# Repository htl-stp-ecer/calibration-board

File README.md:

<div align="center">

# calibration-board

**A companion board for the KIPR Wombat: absolute position from optical flow, and a reference IMU good enough to calibrate the Wombat's own.**

KiCad PCB · STM32F722 firmware · On-board Madgwick fusion · Persistent flash calibration · USB-CDC to LCM bridge

> 📖 Platform documentation at [raccoon-docs.pages.dev](https://raccoon-docs.pages.dev/)

</div>

---

## What this is

There are two things a Wombat can't tell you well on its own.

The first is where it actually is. Wheel odometry integrates encoder ticks and trusts them, but wheels slip on seams, on poms and on ramps, and every slipped tick stays in the estimate for the rest of the run. Encoders measure the wheels, not the ground.

The second is whether its IMU is accurate. The Wombat's onboard IMU is fine for checking that a turn was roughly 90°. It isn't good enough to calibrate anything against.

This board addresses both, and it rides on the robot rather than sitting on a bench:

- A PAA5100 optical flow sensor tracks the table surface. Counts are scaled through a stored calibration into centimetres, which gives the robot an absolute position that doesn't depend on whether a wheel spun.
- An ICM-42688-P with Madgwick fusion on an M7 with an FPU provides a gyro reference accurate enough to calibrate the Wombat's onboard IMU against.

Hence the name. It isn't a board you calibrate, it's the board that does the calibrating.

### What it's for

- Calibrating the onboard IMU, with this board as the reference
- Motion teach-in, recording the trajectory that actually happened rather than the one the encoders inferred
- Automated setup routines. Botball allows automated routines during setup time, which is when a robot can locate and calibrate itself before the run starts

This repo isn't a template. It's a working board with an honest bring-up history attached. Read [Known limitations](#known-limitations) before fabbing one.

---

## Calibration that survives a power cycle

Most of the interesting work is in `app/src/paa_cal_module.c` and `app/inc/calib_store.h`.

Calibration lives in flash rather than in a startup routine. Sector 7 (0x08060000, 128 KB) holds a single 64-byte block: PAA scaling (`cx_per_cm`, `cy_per_cm`, `height_mm`), the gyro bias, a magic number, a schema version and a CRC32. The firmware fits in sectors 0 to 3, so 4 to 7 are free. A bad CRC or empty flash falls back to defaults and reports `valid = false`, so the caller knows it has never been calibrated instead of trusting garbage.

The board boots already calibrated. At startup the stored gyro bias is loaded straight into `imu_fusion_init()`, so there's no warm-up and no need to hold the robot still before a match.

Bias is learned continuously and persisted carefully. While the board is at rest, an exponential moving average runs on the raw gyro, and that average is the bias. It's subtracted before Madgwick and before anything is sent over USB. Auto-save only fires when the learned bias drifts more than 0.5 dps from the stored value, only while at rest so the value is trustworthy, and at most every 2 minutes. Each save costs a full sector erase, roughly 1 s and one P/E cycle, so the threshold and interval keep writes down to a few per large temperature swing. Gyro bias drifts around 0.05 dps/°C, which is what the thresholds are sized for.

Flash writes are deferred out of interrupt context into the main loop via a pending flag, because `HAL_FLASHEx_Erase` blocks.

At-rest detection uses a max-min spread across the gyro axes and accel magnitude, with time dwell and hysteresis. It takes about 0.5 s to declare the board still, and exits immediately on motion. Madgwick runs without a magnetometer at the ICM's 1 kHz ODR, so yaw drifts slowly while roll and pitch stay corrected against gravity. A filter step costs about 1 µs on the M7 at 216 MHz.

Commands over USB: `CMD_SET_PAA_CAL` stores new PAA scaling, `CMD_SAVE_GYRO_BIAS` persists the current at-rest average, `CMD_RESET_GYRO_BIAS` clears it. Telemetry goes the other way, with ORIENTATION frames (quaternion, bias, at-rest flag) at 100 Hz and PAA calibration telemetry at 1 Hz.

---

## How it fits together

```
PAA5100 ─┐                                              ┌─ raccoon/calib_board/paa/delta_x
         ├─ SPI ─► STM32F722 ──► USB-CDC ──► host ──────┤─ raccoon/calib_board/icm/accel
ICM-42688-P ─┘     fusion 1 kHz   binary     bridge     ├─ raccoon/calib_board/icm/gyro
                   cal in flash   frames                └─ raccoon/calib_board/status/*
```

`host/` is a C++ bridge (`raccoon-calib-bridge`) that reads binary frames from `/dev/ttyACM*` and republishes them as typed [raccoon-transport](https://github.com/htl-stp-ecer/raccoon-transport) messages. Calibration data flows on the same LCM channels as everything else in RaccoonOS, so BotUI or any other subscriber can plot it live. Status channels republish every second, which means a subscriber that starts late still picks up the current state instead of waiting for an event. A systemd unit is included.

### Firmware architecture

The module registry is Arduino-style. Each sensor is a `module_t` with `setup()` and `loop()`, registered in one array in `app/src/app.c`. An `enabled` flag parks a module without deleting it, which is how the dead BNO is handled.

Modules are started 25 ms apart rather than all at once. Every peripheral draws current at bring-up, and simultaneous init is a step load that can pull a marginal supply into brownout. Staggering flattens the ramp. The capacitor inrush at plug-in happens before this phase and isn't affected.

---

## Bring-up history

The board was designed around a Bosch BNO086, which does sensor fusion on-chip and outputs a quaternion directly. It never came up. After reset the INT line asserts, but the BNO never actively drives MISO, so every packet we read was a threshold artefact from a floating line. SPI mode, clock speed, pull-ups, boot delay and pin states were all ruled out in software, which left a suspected broken CS path. It's parked in the firmware with `.enabled = false /* BNO08x defekt */`.

The ICM-42688-P took over instead: raw 6-axis, with fusion left to us. That's why `imu_fusion.c` exists. Losing the chip that would have done fusion internally is what moved Madgwick onto the STM32, where the bias estimator could be added and the whole pipeline is visible rather than hidden behind a sensor hub.

The HSE crystal also refused to oscillate at first, leaving `HSEON=1, HSERDY=0` and dropping into `Error_Handler` on every boot. That turned out to be an oscillator ground problem and was fixed in the schematic. The firmware runs on HSE now.

---

## Repo layout

| Path | Contents |
|:-----|:---------|
| `Firmware/` | STM32CubeMX CMake project, target STM32F722RET6. Capitalised folders are ST-generated, lowercase are ours |
| `Firmware/app/` | Module registry, fusion, calibration store, USB framing |
| `Firmware/drivers/` | Our chip drivers: `bno08x/`, `icm42688p/`, `paa5100/` |
| `Firmware/lib/sh2/` | CEVA BNO08x driver (git submodule) |
| `Firmware/scripts/` | build / flash / debug / uart / swo. Call these rather than ST tools directly |
| `host/` | C++ USB-CDC to raccoon-transport bridge, plus systemd unit |
| `IMU_Extendor_Board/` | KiCad 7+ project: schematic, PCB, BOM, gerbers in `production/` |
| `enclosure/` | OpenSCAD tray and lid, STL/STEP exports (M2 self-tapping, ~55x55 mm PCB) |
| `Component_Datasheets/` | Datasheets plus hand-written analysis (`external_clock_analysis.md`) |
| `docs/` | Toolchain setup, firmware workflow, hardware overview, coding conventions |

---

## Quick start

```bash
git submodule update --init --recursive   # sh2 + raccoon-transport

Firmware/scripts/build.sh          # cmake + ninja
Firmware/scripts/build-docker.sh   # same, in a container, no host arm-gcc needed
Firmware/scripts/flash.sh          # build + flash + verify + start over ST-LINK SWD
Firmware/scripts/uart.sh           # stream the debug console (J703, 115200 8N1)
```

Full setup for a fresh machine: [`docs/toolchain-setup.md`](docs/toolchain-setup.md).

### Catching boot output

Start `uart.sh` before `flash.sh`. The boot `printf` fires within milliseconds of reset, well before you can switch terminals. Two panes:

```bash
# Pane 1, left running:
Firmware/scripts/uart.sh
# Pane 2:
Firmware/scripts/flash.sh
```

If an expected printf never appears, the firmware is more likely hung before that line than the UART is broken. Init exposes debug globals (`g_bno_init_status`, `g_paa_init_status`, `g_bno_stage`, `g_paa_cal_loaded`) that you can read over SWD without re-flashing:

```bash
STM32_Programmer_CLI -c port=SWD mode=HOTPLUG -r32 <addr> 4
```

### The USER LED is a status channel

With no UART adapter attached, the LED is the only thing reporting anything:

| Pattern | Meaning |
|:--------|:--------|
| 100 ms on / 100 ms off (fast) | init OK, sensor answered, product IDs read |
| 500 ms on / 500 ms off (slow) | setup failed, INT line or clock path suspect |
| 50 ms on / 950 ms off (pulse) | unexpected init return code |

---

## Known limitations

Worth reading before you fab a board or trust a number.

- The BNO086 is dead and disabled. A broken CS path is the suspicion. Software causes were ruled out, so it needs a DMM on `PA4` to `BNO086 CSN` before anyone touches the firmware again.
- USB-C (J101) is not populated. The board runs off the ST-LINK debug cable, which caps its current budget and means it isn't standalone. J101 and the USBLC6 ESD diode need populating per the schematic before it can ride on a robot properly.
- SWO doesn't work with ST-LINK V2 clones. `swo_init` configures TPIU/ITM correctly, but the green clones expose a `T_JTDO` pin that isn't internally wired to their TRACESWO input, and reflashing official ST firmware doesn't fix it. Use UART4 instead, or a genuine STLINK-V3. `__io_putchar` writes to both sinks, so take whichever you can capture.
- PAA scaling depends on mount height. The defaults assume 19 mm. Changing the height changes counts-per-cm, so recalibrate via `CMD_SET_PAA_CAL` after any remount or the absolute position will be confidently wrong.
- The flash layout assumes small firmware. The calibration block sits in sector 7 because the code fits in sectors 0 to 3. Firmware growing past about 448 KB breaks that.
- Chip-select assignments aren't fully captured in the firmware. Cross-reference the KiCad schematic before wiring up a new sensor.
- `Firmware.ioc` is owned by CubeMX. Regenerating overwrites most of `Core/` and `Drivers/`, so keep code inside the `USER CODE BEGIN/END` markers, or put it in `app/` and call it from `app_main()`.
- Parts of the docs and code comments are in German. This was an internal engineering repo and we haven't translated it.

---

## Part of RaccoonOS

| Repository | What it is |
|:-----------|:-----------|
| [raccoon-transport](https://github.com/htl-stp-ecer/raccoon-transport) | The LCM messaging layer this board publishes into |
| [stm32-data-reader](https://github.com/htl-stp-ecer/stm32-data-reader) | Pi to STM32 SPI bridge on the robot itself |
| [raccoon-lib](https://github.com/htl-stp-ecer/raccoon-lib) | Core robotics library, odometry and heading control downstream of this |
| [raccoon-robots](https://github.com/htl-stp-ecer/raccoon-robots) | Real competition robots built on the platform |
| [botui](https://github.com/htl-stp-ecer/botui) | Wombat dashboard, can subscribe to these channels live |
| [documentation](https://raccoon-docs.pages.dev/) | Full platform docs |

---

Built by team `axht-3085`, the Botball team at HTL St. Pölten.

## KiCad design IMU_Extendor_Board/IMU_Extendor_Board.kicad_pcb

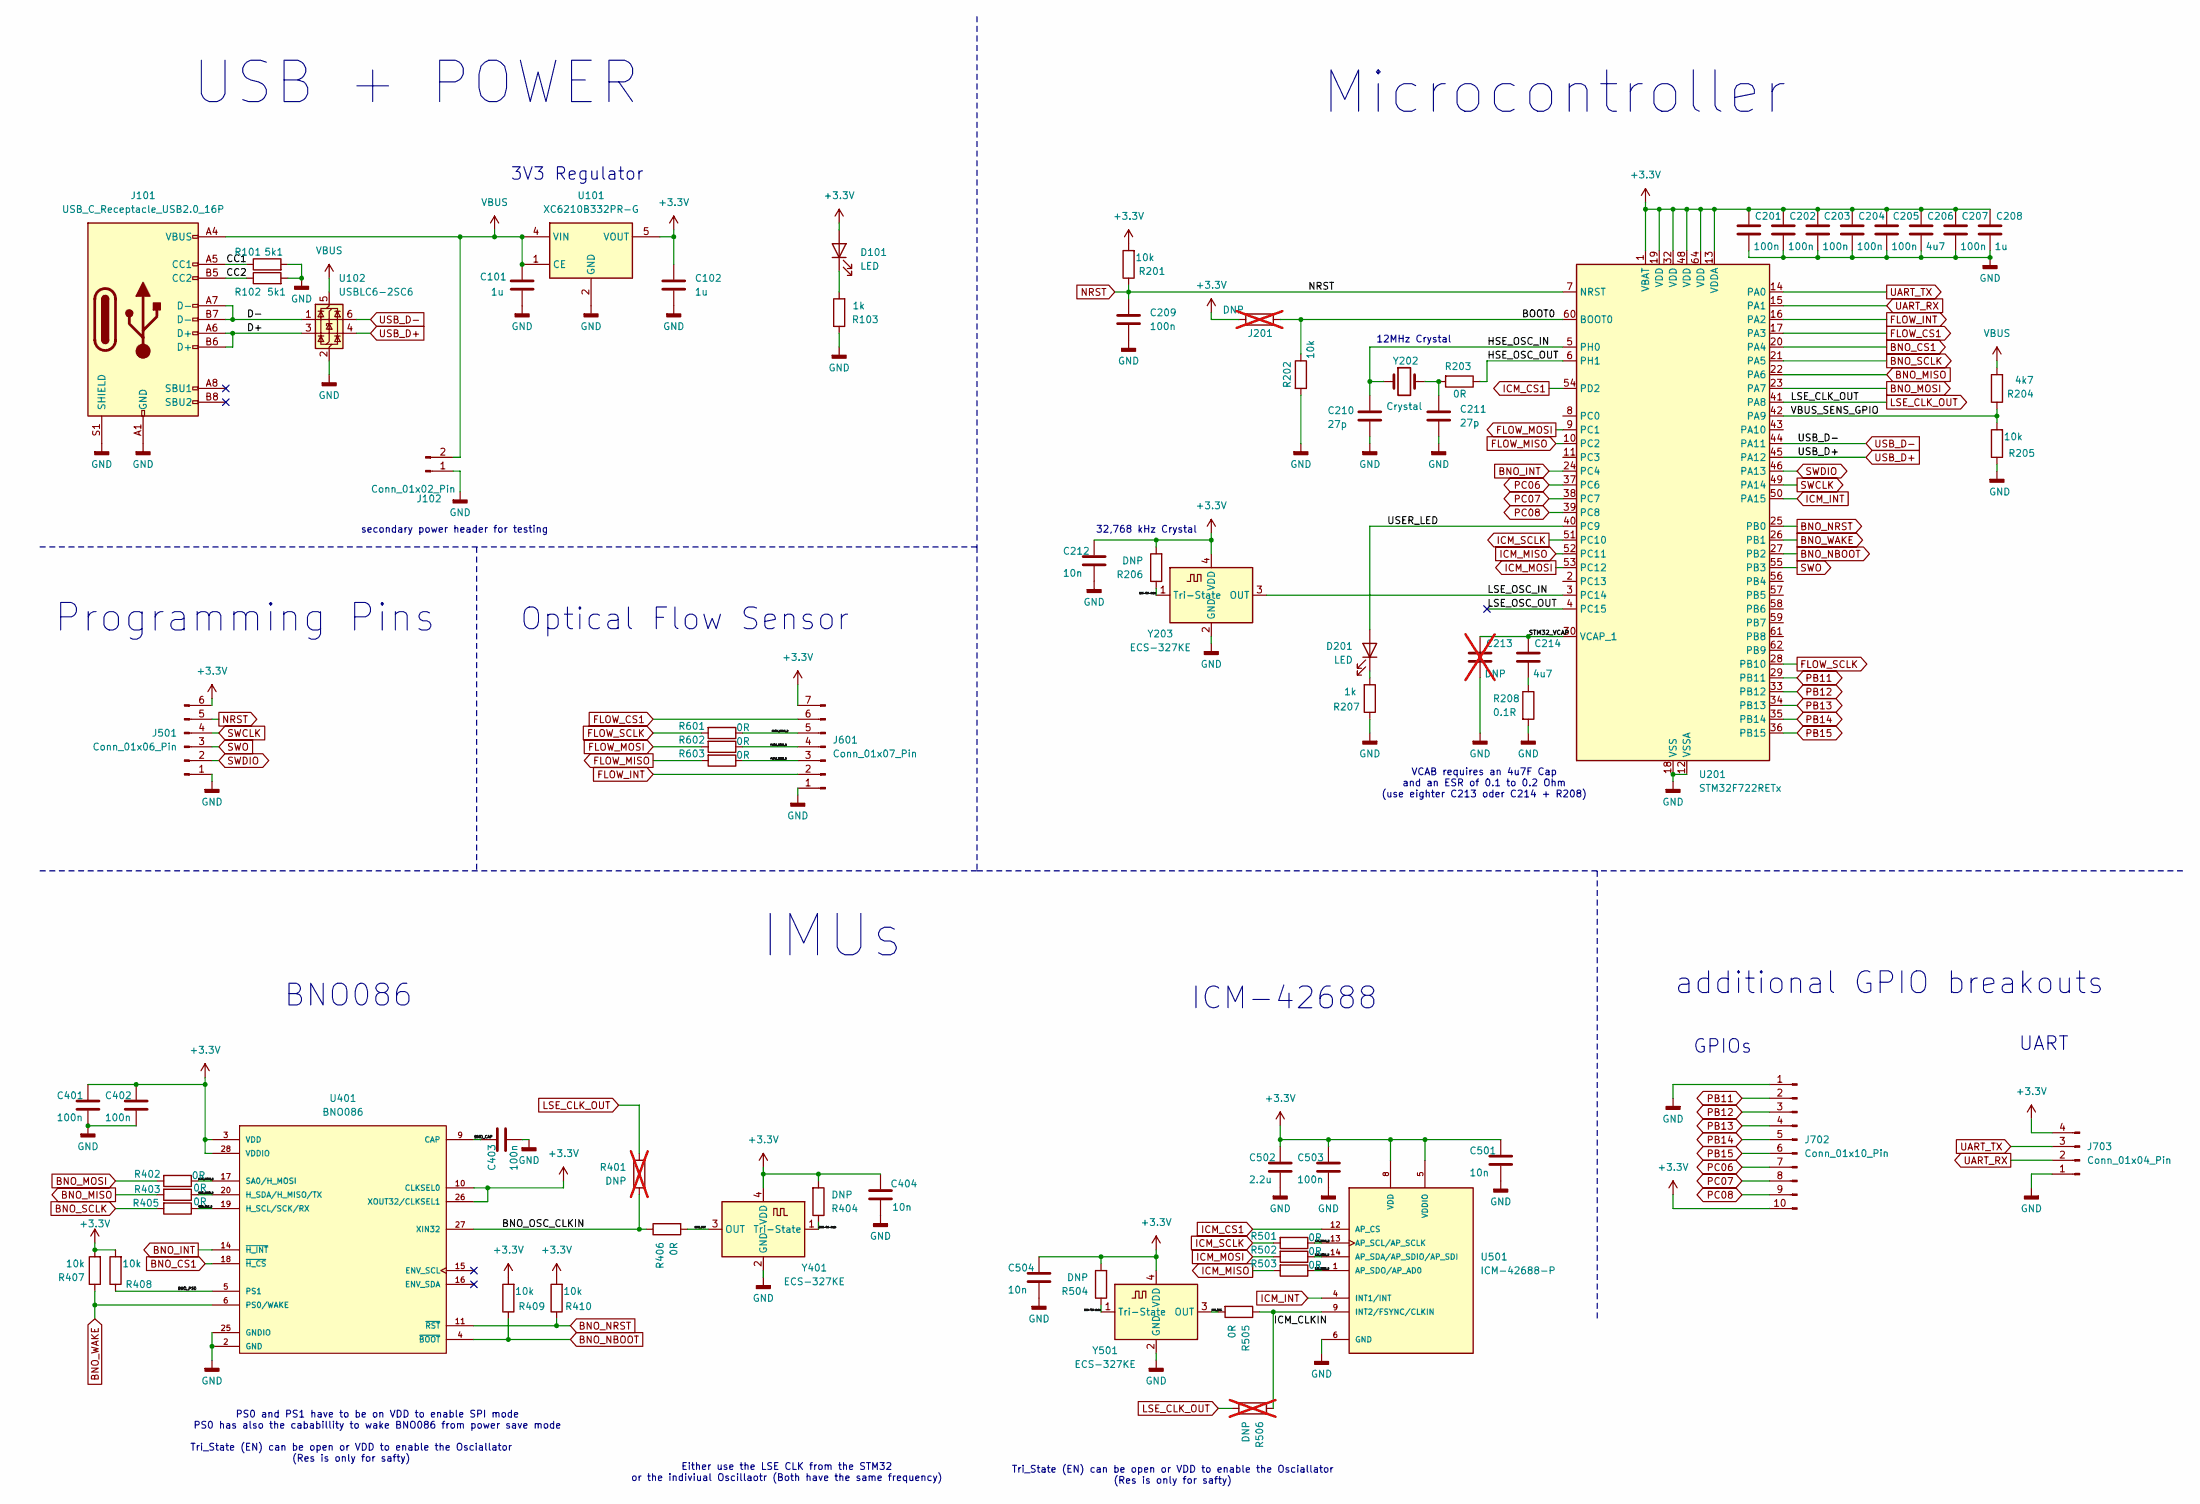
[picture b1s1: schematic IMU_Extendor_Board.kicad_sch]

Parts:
C101, C102: 1u; C_0805_2012Metric_Pad1.18x1.45mm_HandSolder
C201, C202, C203, C204, C205, C207, C209, C401, C402, C403, C503: 100n; 0402_1005Metric_Pad0.74x0.62mm_HandSolder
C206, C214: 4u7; C_0603_1608Metric_Pad1.08x0.95mm_HandSolder
C208: 1u; C_0603_1608Metric_Pad1.08x0.95mm_HandSolder
C210, C211: 27p; 0402_1005Metric_Pad0.74x0.62mm_HandSolder
C212, C404, C501, C504: 10n; 0402_1005Metric_Pad0.74x0.62mm_HandSolder
C213: DNP; C_0603_1608Metric_Pad1.08x0.95mm_HandSolder; not fitted
C502: 2.2u; C_0603_1608Metric
D101, D201: LED; LED_0603_1608Metric
J101: USB_C_Receptacle_USB2.0_16P; USB_C_Receptacle_GCT_USB4105-xx-A_16P_TopMnt_Horizontal
J102: Conn_01x02_Pin; PinHeader_1x02_P2.54mm_Vertical
J201: DNP; R_0805_2012Metric_Pad1.20x1.40mm_HandSolder; not fitted
J501: Conn_01x06_Pin; PinHeader_1x06_P2.54mm_Vertical
J601: Conn_01x07_Pin; PinHeader_1x07_P2.54mm_Vertical
J702: Conn_01x10_Pin; PinHeader_1x10_P1.27mm_Vertical_SMD_Pin1Right
J703: Conn_01x04_Pin; PinHeader_1x04_P2.54mm_Vertical
R101, R102: 5k1; 0402_1005Metric_Pad0.74x0.62mm_HandSolder
R103, R207: 1k; 0402_1005Metric_Pad0.74x0.62mm_HandSolder
R201, R202, R205, R407, R408, R409, R410: 10k; 0402_1005Metric_Pad0.74x0.62mm_HandSolder
R203, R402, R403, R405, R406, R501, R502, R503, R505, R601, R602, R603: 0R; 0402_1005Metric_Pad0.74x0.62mm_HandSolder
R204: 4k7; 0402_1005Metric_Pad0.74x0.62mm_HandSolder
R206, R404, R504: DNP; 0402_1005Metric_Pad0.74x0.62mm_HandSolder
R208: 0.1R; 0402_1005Metric_Pad0.74x0.62mm_HandSolder
R401, R506: DNP; 0402_1005Metric_Pad0.74x0.62mm_HandSolder; not fitted
U101: XC6210B332PR-G; SOT-89-5_Handsoldering
U102: USBLC6-2SC6; SOT-23-6
U201: STM32F722RETx; LQFP-64_10x10mm_P0.5mm
U401: BNO086
U501: ICM-42688-P; ICM-42688-p
Y202: Crystal; Crystal_SMD_Abracon_ABM8G-4Pin_3.2x2.5mm
Y203, Y401, Y501: ECS-327KE; Oscillator_SMD_ECS_2520MV-xxx-xx-4Pin_2.5x2.0mm

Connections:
+3.3V: C102.1, C201.1, C202.1, C203.1, C204.1, C205.1, C206.1, C207.1, C208.1, C212.1, C401.1, C402.1, C404.1, C501.1, C502.1, C503.1, C504.1, D101.2 (A), J201.1, J501.6, J601.7, J702.10, J703.4, R201.2, R206.2, R404.2, R407.2, R408.2, R409.2, R410.2, R504.2, U101.5 (VOUT), U201.1 (VBAT), U201.13 (VDDA), U201.19 (VDD), U201.32 (VDD), U201.48 (VDD), U201.64 (VDD), U401.3 (VDD), U401.10 (CLKSEL0), U401.26 (XOUT32/CLKSEL1), U401.28 (VDDIO), U501.5 (VDDIO), U501.8 (VDD), Y203.4 (VDD), Y401.4 (VDD), Y501.4 (VDD); also elsewhere on the board
/BNO-Tri-Sate: R404.1, Y401.1 (Tri-State)
/BNO_CAP: C403.1, U401.9 (CAP)
/BNO_CLK_D: R405.1, U401.19 (H_SCL/SCK/RX)
/BNO_EVN_SCL: U401.15 (ENV_SCL); also elsewhere on the board
/BNO_EVN_SDA: U401.16 (ENV_SDA); also elsewhere on the board
/BNO_MISO_D: R403.1, U401.20 (H_SDA/H_MISO/TX)
/BNO_MOSI_D: R402.1, U401.17 (SA0/H_MOSI)
/BNO_OSC: R406.2, Y401.3 (OUT)
/BNO_OSC_CLKIN: R401.2, R406.1, U401.27 (XIN32)
/BNO_PS0: R408.1, U401.5 (PS1)
/BOOT0: J201.2, R202.1, U201.60 (BOOT0)
/CC1: J101.A5 (CC1), R101.1
/CC2: J101.B5 (CC2), R102.1
/D+: J101.A6 (D+), J101.B6 (D+), U102.3 (I/O2)
/D-: J101.A7 (D-), J101.B7 (D-), U102.1 (I/O1)
/FLOW_MISO_D: J601.3, R603.1
/FLOW_MOSI_D: J601.4, R602.1
/FLOW_SCLK_D: J601.5, R601.1
/HSE_OSC_IN: C210.1, U201.5 (PH0), Y202.1; also elsewhere on the board
/HSE_OSC_OUT: R203.1, U201.6 (PH1)
/ICM-Tri-Sate: R504.1, Y501.1 (Tri-State)
/ICM_CLKIN: R505.1, R506.1, U501.9 (INT2/FSYNC/CLKIN)
/ICM_MISO_D: R503.1, U501.1 (AP_SDO/AP_AD0)
/ICM_MOSI_D: R502.1, U501.14 (AP_SDA/AP_SDIO/AP_SDI)
/ICM_OSC: R505.2, Y501.3 (OUT)
/ICM_SCLK_D: R501.1, U501.13 (AP_SCL/AP_SCLK)
/LSE-Tri-Sate: R206.1, Y203.1 (Tri-State)
/LSE_OSC_IN: U201.3 (PC14), Y203.3 (OUT)
/LSE_OSC_OUT: U201.4 (PC15)
/STM32_VCAP: C213.1, C214.1, U201.30 (VCAP_1)
/USER_LED: D201.2 (A), U201.40 (PC9)
/VBUS_SENS_GPIO: R204.1, R205.2, U201.42 (PA9)
BNO_CS1: U201.20 (PA4), U401.18 (~H_CS)
BNO_INT: U201.24 (PC4), U401.14 (~H_INT)
BNO_MISO: R403.2, U201.22 (PA6)
BNO_MOSI: R402.2, U201.23 (PA7)
BNO_SCLK: R405.2, U201.21 (PA5)
BNO_WAKE: R407.1, U201.26 (PB1), U401.6 (PS0/WAKE)
FLOW_CS1: J601.6, U201.17 (PA3)
FLOW_INT: J601.2, U201.16 (PA2)
FLOW_MISO: R603.2, U201.10 (PC2)
FLOW_MOSI: R602.2, U201.9 (PC1)
FLOW_SCLK: R601.2, U201.28 (PB10)
GND: C101.2, C102.2, C201.2, C202.2, C203.2, C204.2, C205.2, C206.2, C207.2, C208.2, C209.2, C210.2, C211.2, C212.2, C213.2, C401.2, C402.2, C403.2, C404.2, C501.2, C502.2, C503.2, C504.2, J101.A1 (GND), J101.A12 (GND), J101.B1 (GND), J101.B12 (GND), J101.S1 (SHIELD), J102.1, J501.1, J601.1, J702.1, J703.1, R101.2, R102.2, R103.1, R202.2, R205.1, R207.1, R208.2, U101.2 (GND), U102.2 (GND), U201.12 (VSSA), U201.18 (VSS), U201.31 (VSS), U201.47 (VSS), U201.63 (VSS), U401.2 (GND), U401.25 (GNDIO), U501.6 (GND), Y203.2 (GND), Y401.2 (GND), Y501.2 (GND); also elsewhere on the board
ICM_CS1: U201.54 (PD2), U501.12 (AP_CS)
ICM_INT: U201.50 (PA15), U501.4 (INT1/INT)
ICM_MISO: R503.2, U201.52 (PC11)
ICM_MOSI: R502.2, U201.53 (PC12)
ICM_SCLK: R501.2, U201.51 (PC10)
LSE_CLK_OUT: R401.1, R506.2, U201.41 (PA8)
NRST: C209.1, J501.5, R201.1, U201.7 (NRST)
unnamed 52: C211.1, R203.2, Y202.3; also elsewhere on the board
unnamed: C214.2, R208.1
unnamed: D101.1 (K), R103.2
unnamed: D201.1 (K), R207.2
PB11: J702.2, U201.29 (PB11)
PB12: J702.3, U201.33 (PB12)
PB13: J702.4, U201.34 (PB13)
PB14: J702.5, U201.35 (PB14)
PB15: J702.6, U201.36 (PB15)
PC06: J702.7, U201.37 (PC6)
PC07: J702.8, U201.38 (PC7)
PC08: J702.9, U201.39 (PC8)
SWCLK: J501.4, U201.49 (PA14)
SWDIO: J501.2, U201.46 (PA13)
SWO: J501.3, U201.55 (PB3)
UART_RX: J703.2, U201.15 (PA1)
UART_TX: J703.3, U201.14 (PA0)
USB_D+: U102.4 (I/O2), U201.45 (PA12)
USB_D-: U102.6 (I/O1), U201.44 (PA11)
VBUS: C101.1, J101.A4 (VBUS), J101.A9 (VBUS), J101.B4 (VBUS), J101.B9 (VBUS), J102.2, R204.2, U101.1 (CE), U101.4 (VIN), U102.5 (VBUS)

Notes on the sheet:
ICM-42688
additional GPIO breakouts
PS0 and PS1 have to be on VDD to enable SPI mode PS0 has also the cababillity to wake BNO086 from power save mode
Either use the LSE CLK from the STM32 or the indiviual Oscillaotr (Both have the same frequency)
secondary power header for testing
Optical Flow Sensor
12MHz Crystal
BNO086
VCAB requires an 4u7F Cap and an ESR of 0.1 to 0.2 Ohm (use eighter C213 oder C214 + R208)
Tri_State (EN) can be open or VDD to enable the Osciallator (Res is only for safty)
Microcontroller
Programming Pins
3V3 Regulator
GPIOs
IMUs
UART
USB + POWER
32,768 kHz Crystal

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
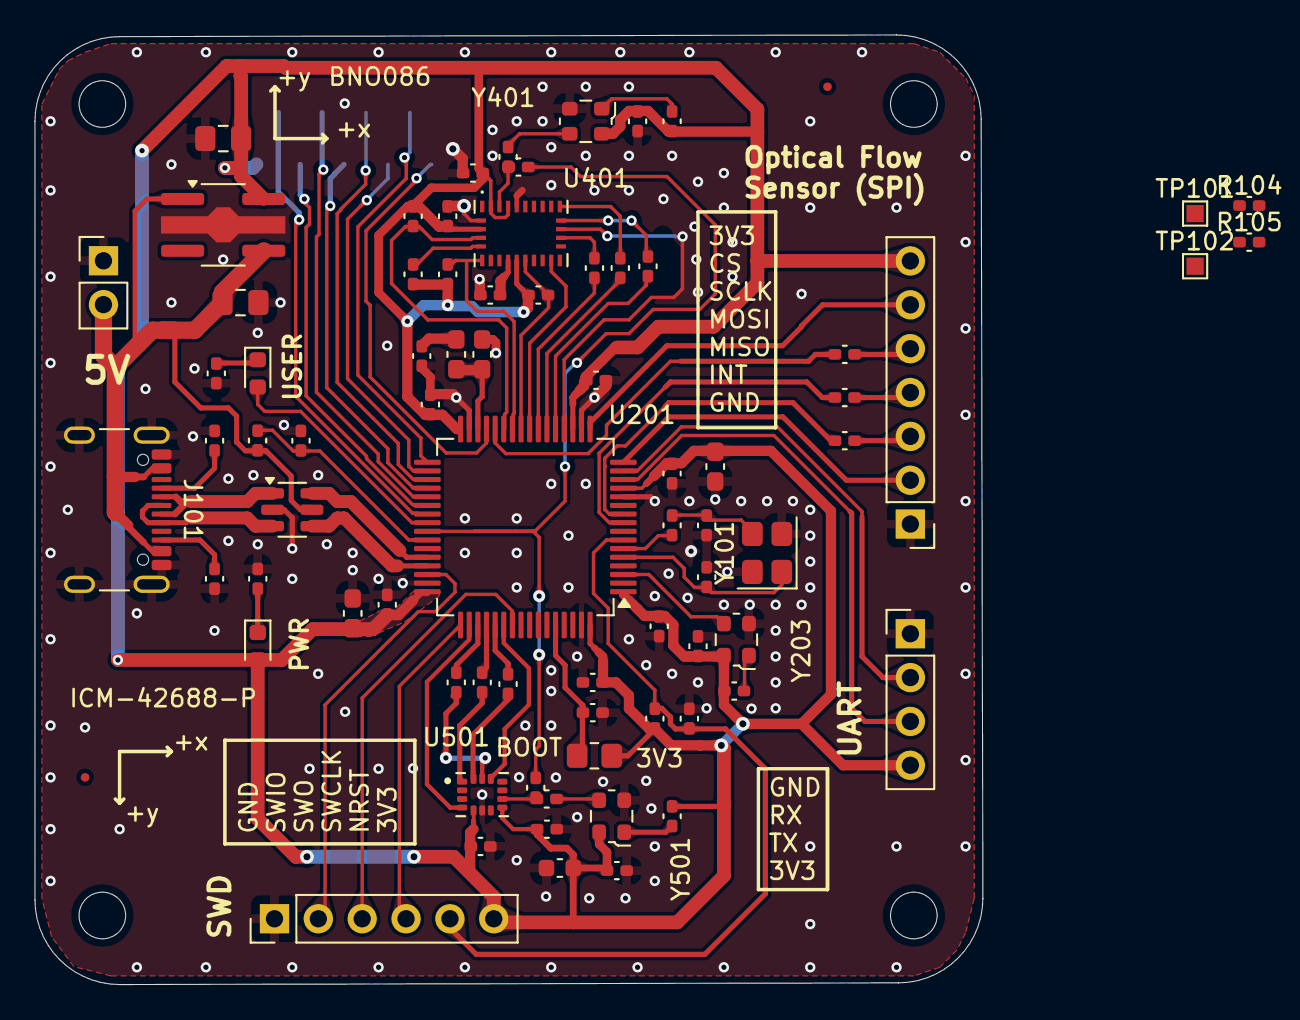
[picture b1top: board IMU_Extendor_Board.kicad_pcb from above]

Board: 2 copper layers, 54.9 x 55.0 mm, 76 parts (1 on the bottom side), 73 nets.

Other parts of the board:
R104, R105: 2k2; 0402_1005Metric_Pad0.74x0.62mm_HandSolder
TP101, TP102: TestPoint; TestPoint_Pad_1.0x1.0mm
Y101: Crystal_GND24; Crystal_SMD_Abracon_ABM8G-4Pin_3.2x2.5mm

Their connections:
+3.3V: R104.2, R105.2; also elsewhere on the board
/BNO_EVN_SCL: R104.1, TP102.1; also elsewhere on the board
/BNO_EVN_SDA: R105.1, TP101.1; also elsewhere on the board
/HSE_OSC_IN: Y101.1; also elsewhere on the board
GND: Y101.2, Y101.4; also elsewhere on the board
unnamed 52: Y101.3; also elsewhere on the board

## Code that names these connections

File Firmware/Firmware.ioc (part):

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Mcu.Name=STM32F722R(C-E)Tx
Mcu.Package=LQFP64
Mcu.UserName=STM32F722RETx
PA0-WKUP.Mode=Asynchronous
PA0-WKUP.Signal=UART4_TX
PA1.Mode=Asynchronous
PA1.Signal=UART4_RX
PA11.Mode=Device_Only
PA11.Signal=USB_OTG_FS_DM
PA12.Mode=Device_Only
PA12.Signal=USB_OTG_FS_DP
PA13.Mode=Trace_Asynchronous_SW
PA13.Signal=SYS_JTMS-SWDIO
PA14.Mode=Trace_Asynchronous_SW
PA14.Signal=SYS_JTCK-SWCLK
PA15.GPIOParameters=GPIO_Label
PA15.GPIO_Label=ICM_INT
PA15.Signal=GPXTI15
PA2.GPIOParameters=GPIO_PuPd,GPIO_Label
PA2.GPIO_Label=FLOW_SENS_INT
PA2.GPIO_PuPd=GPIO_PULLUP
PA2.Signal=GPIO_Input
PA3.GPIOParameters=PinState,GPIO_Label
PA3.GPIO_Label=FLOW_SENS_CS
PA3.PinState=GPIO_PIN_SET
PA3.Signal=GPIO_Output
PA4.GPIOParameters=PinState,GPIO_Label
PA4.GPIO_Label=BNO_CS1
PA4.PinState=GPIO_PIN_SET
PA4.Signal=GPIO_Output
PA5.GPIOParameters=GPIO_Label
PA5.GPIO_Label=BNO_SCLK
PA5.Mode=Full_Duplex_Master
PA5.Signal=SPI1_SCK
PA6.GPIOParameters=GPIO_Label
PA6.GPIO_Label=BNO_MISO
PA6.Mode=Full_Duplex_Master
PA6.Signal=SPI1_MISO
PA7.GPIOParameters=GPIO_Label
PA7.GPIO_Label=BNO_MOSI
PA7.Mode=Full_Duplex_Master
PA7.Signal=SPI1_MOSI
PA9.Mode=Activate_VBUS
PA9.Signal=USB_OTG_FS_VBUS
PB0.GPIOParameters=PinState,GPIO_Label
PB0.GPIO_Label=BNO_NRST
PB0.PinState=GPIO_PIN_SET
PB0.Signal=GPIO_Output
PB1.GPIOParameters=PinState,GPIO_Label
PB1.GPIO_Label=BNO_WAKE
PB1.PinState=GPIO_PIN_SET
PB1.Signal=GPIO_Output
PB10.Mode=Full_Duplex_Master
PB10.Signal=SPI2_SCK
PB11.GPIOParameters=GPIO_Label
PB11.GPIO_Label=add_PB11
PB11.Signal=GPIO_Output
PB12.GPIOParameters=GPIO_Label
PB12.GPIO_Label=add_PB12
PB12.Signal=GPIO_Output
PB13.GPIOParameters=GPIO_Label
PB13.GPIO_Label=add_PB13
PB13.Signal=GPIO_Output
PB14.GPIOParameters=GPIO_Label
PB14.GPIO_Label=add_PB14
PB14.Signal=GPIO_Output
PB15.GPIOParameters=GPIO_Label
PB15.GPIO_Label=add_PB15
PB15.Signal=GPIO_Output
PB2.GPIOParameters=PinState,GPIO_Label
PB2.GPIO_Label=BNO_NBOOT
PB2.PinState=GPIO_PIN_SET
PB2.Signal=GPIO_Output
PB3.Mode=Trace_Asynchronous_SW
PB3.Signal=SYS_JTDO-SWO
PC1.GPIOParameters=GPIO_Label
PC1.GPIO_Label=FLOW_MOSI
PC1.Mode=Full_Duplex_Master
PC1.Signal=SPI2_MOSI
PC10.Mode=Full_Duplex_Master
PC10.Signal=SPI3_SCK
PC11.Mode=Full_Duplex_Master
PC11.Signal=SPI3_MISO
PC12.Mode=Full_Duplex_Master
PC12.Signal=SPI3_MOSI
PC14-OSC32_IN.Mode=LSE-External-Clock-Source
PC14-OSC32_IN.Signal=RCC_OSC32_IN
PC15-OSC32_OUT.Mode=LSE-External-Clock-Source
PC15-OSC32_OUT.Signal=RCC_OSC32_OUT
PC2.Mode=Full_Duplex_Master
PC2.Signal=SPI2_MISO
PC4.GPIOParameters=GPIO_PuPd,GPIO_Label,GPIO_ModeDefaultEXTI
PC4.GPIO_Label=BNO_INT
PC4.GPIO_ModeDefaultEXTI=GPIO_MODE_IT_FALLING
PC4.GPIO_PuPd=GPIO_PULLUP
PC4.Signal=GPXTI4
PC6.GPIOParameters=GPIO_Label
PC6.GPIO_Label=add_PC6
PC6.Signal=GPIO_Output
PC7.GPIOParameters=GPIO_Label
PC7.GPIO_Label=add_PC7
PC7.Signal=GPIO_Output
PC8.GPIOParameters=GPIO_Label
PC8.GPIO_Label=add_PC8
PC8.Signal=GPIO_Output
PC9.GPIOParameters=GPIO_Label
PC9.GPIO_Label=USER_LED
PC9.Signal=GPIO_Output
PD2.GPIOParameters=PinState,GPIO_Label
PD2.GPIO_Label=SPI3_CS1
PD2.PinState=GPIO_PIN_SET
PD2.Signal=GPIO_Output
PH0-OSC_IN.Mode=HSE-External-Oscillator
PH0-OSC_IN.Signal=RCC_OSC_IN
PH1-OSC_OUT.Mode=HSE-External-Oscillator
PH1-OSC_OUT.Signal=RCC_OSC_OUT
RCC.HSE_VALUE=12000000
RCC.SYSCLKFreq_VALUE=192000000
RCC.SYSCLKSource=RCC_SYSCLKSOURCE_PLLCLK
board=custom

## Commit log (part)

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2026-05-20 add initial project files and setup scripts for STM32 calibration board firmware
2026-05-20 add application logic and hardware driver integration for BNO08x and PAA5100
2026-05-20 update GPIO configurations and SPI settings for improved functionality
2026-05-20 tobi wanted a commit :) + code gen
2026-05-21 bno08x bringup: NRST/BOOTN PinState fix + diagnostic counters
    - .ioc: PB0 (BNO_NRST) PinState=SET — without this, MX_GPIO_Init holds
    the BNO in reset until bno08x_init runs, leaving the chip in an
    inconsistent power-on state. Sibling fix to the existing BOOTN/PB2
    default-HIGH config.
    - main.c: HSI workaround for SystemClock_Config restored (HSE crystal
    Y202 still not soldered cleanly — Issue 1). Reverted on every CubeMX
2026-05-21 optical flow + hse working
2026-05-21 modifide the schematic to fix oscillator GND and in pcb; added ENV I2C pullpus in shematic
2026-05-21 cs line works but MISO doesn't send any data; added pullups on int and miso lines because claude told me too
2026-05-29 add USB device support with CDC class integration and descriptors
2026-06-06 add ICM42688P sensor support and update USB module for binary frame streaming
2026-06-06 update IMU data handling to include bias_z and adjust payload sizes for orientation frame
2026-06-16 add PAA_ACC frame support and implement signed counts accumulator for motion tracking
